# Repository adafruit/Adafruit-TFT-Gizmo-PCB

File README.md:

## Adafruit Circuit Playground TFT Gizmo - Bolt-on Display + Audio Amplifier PCB

<a href="http://www.adafruit.com/products/4367"><br/>
Click here to purchase one from the Adafruit shop</a>

PCB files for the Adafruit Circuit Playground TFT Gizmo - Bolt-on Display + Audio Amplifier. 

Format is EagleCAD schematic and board layout
* https://www.adafruit.com/product/4367

### Description

Extend and expand your Circuit Playground projects with a bolt on TFT Gizmo that lets you add a lovely color display in a sturdy and reliable fashion. This PCB looks just like a round TFT breakout but has permanently affixed M3 standoffs that act as mechanical and electrical connections.

Once attached you'll get a 1.54" 240x240 IPS display with backlight control, two 3-pin STEMMA connectors for attaching NeoPixel strips or servos, and a Class D audio amplifier with a Molex PicoBlade connector that can plug one of our lil speakers.

This is a great companion for our Circuit Playground Express or Bluefruit boards thanks to their fast SPI hardware speeds, and works in Arduino and CircuitPython. You can use it with the Circuit Playground Classic but it won't be very fast, as you have to bitbang the SPI - and the display has a lot of pixels - so it's not recommended.

Comes with a PCB that has pre-soldered standoffs attached, and 12x M3 screws for attachment. Fits all Circuit Playgrounds but like we mentioned earlier, the Express and Bluefruit are recommended.

### License

Adafruit invests time and resources providing this open source design, please support Adafruit and open-source hardware by purchasing products from [Adafruit](https://www.adafruit.com)!

Designed by Limor Fried/Ladyada for Adafruit Industries.

Creative Commons Attribution/Share-Alike, all text above must be included in any redistribution. 
See license.txt for additional details.

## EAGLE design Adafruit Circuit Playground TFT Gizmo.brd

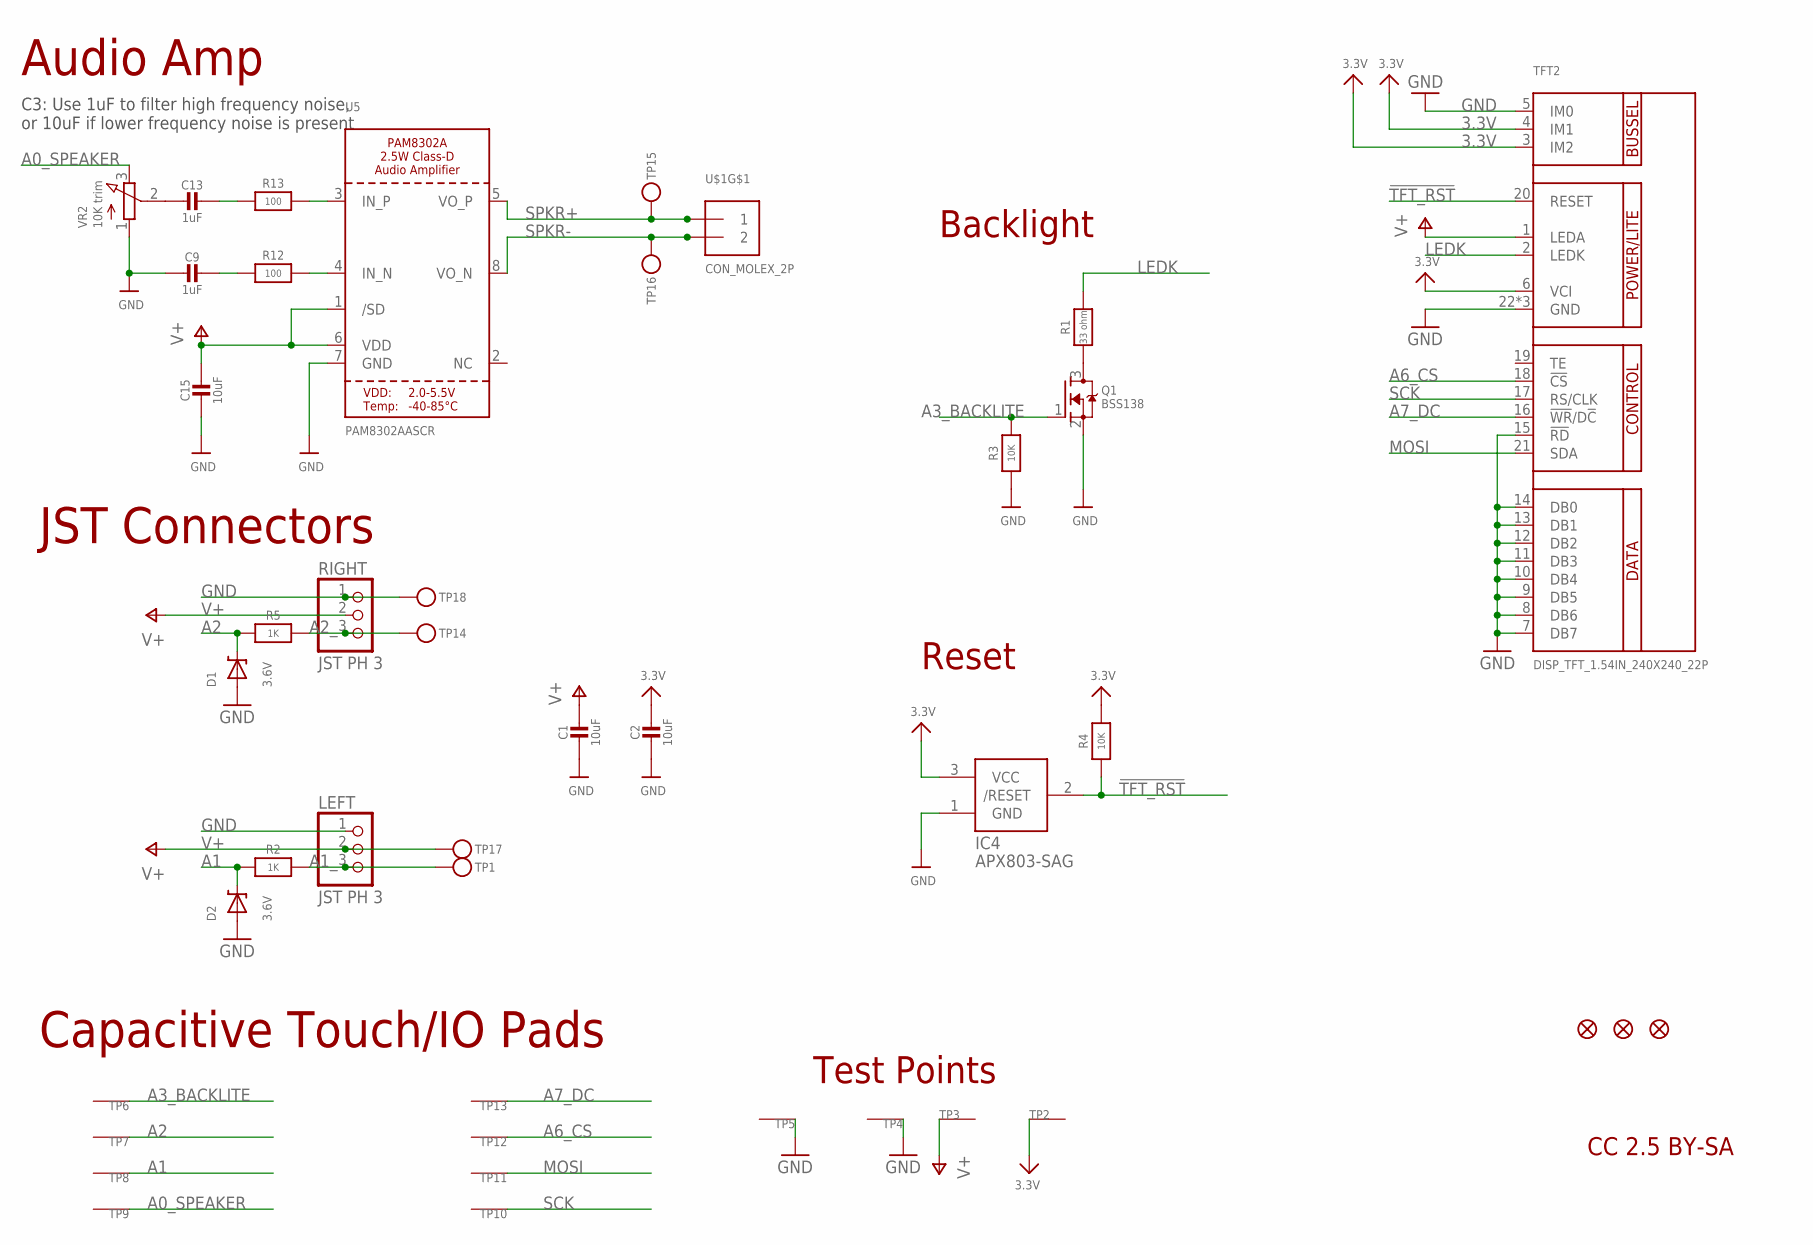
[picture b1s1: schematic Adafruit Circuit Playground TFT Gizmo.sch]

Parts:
C1, C2, C15: 10uF; 0805-NO
C9, C13: 1uF; 0603-NO
D1, D2: 3.6V; SOD-323
IC4: APX803-SAG; SOT23
LEFT: JST PH 3; JSTPH3
Q1: BSS138; SOT23-WIDE
R1: 33 ohm; 0603-NO
R2, R5: 1K; 0603-NO
R3, R4: 10K; 0603-NO
R12, R13: 100; 0603-NO
RIGHT: JST PH 3; JSTPH3
TFT2: DISP_TFT_1.54IN_240X240_22P; TFT_1.54IN_240X240_22PIN
TP1, TP14, TP15, TP16, TP17, TP18: TESTPOINTROUND1.5MMNO; TESTPOINT_ROUND_1.5MM_NO
TP2, TP3, TP4, TP5, TP6, TP7, TP8, TP9, TP10, TP11, TP12, TP13: SEWTAP_SMTNUTM3; SMT_NUT_3MM
U5: PAM8302AASCR; MSOP8_0.65MM
U$1: CON_MOLEX_2P; 53398-0271
U$2, U$3, U$6: FIDUCIAL_1MM
VR2: 10K trim; TRIMPOT_BOURNS_3303W

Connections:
3.3V: C2.1, IC4.3 (VCC), R4.2, TFT2.3 (IM2), TFT2.4 (IM1), TFT2.6 (VCI), TP2.P$1
!TFT_RST: IC4.2 (/RESET), R4.1, TFT2.20 (RESET)
A0_SPEAKER: TP9.P$1, VR2.3 (E)
A1: D2.C, R2.2, TP8.P$1
A1_: LEFT.3, R2.1, TP1.P$1
A2: D1.C, R5.2, TP7.P$1
A2_: R5.1, RIGHT.3, TP14.P$1
A3_BACKLITE: Q1.1 (G), R3.2, TP6.P$1
A6_CS: TFT2.18 (!CS), TP12.P$1
A7_DC: TFT2.16 (!WR!/D!C), TP13.P$1
GND: C1.2, C2.2, C9.2, C15.2, D1.A, D2.A, IC4.1 (GND), LEFT.1, Q1.2 (S), R3.1, RIGHT.1, TFT2.5 (IM0), TFT2.7 (DB7), TFT2.8 (DB6), TFT2.9 (DB5), TFT2.10 (DB4), TFT2.11 (DB3), TFT2.12 (DB2), TFT2.13 (DB1), TFT2.14 (DB0), TFT2.15 (!RD), TFT2.22 (GND), TFT2.SUPPORT1 (GND), TFT2.SUPPORT2 (GND), TP4.P$1, TP5.P$1, TP18.P$1, U5.7 (GND), VR2.1 (A)
LEDK: R1.2, TFT2.2 (LEDK)
MOSI: TFT2.21 (SDA), TP11.P$1
unnamed: Q1.3 (D), R1.1
unnamed: R12.2, U5.4 (IN_N)
unnamed: R13.2, U5.3 (IN_P)
unnamed: C9.1, R12.1
unnamed: C13.1, R13.1
unnamed: C13.2, VR2.2 (S)
SCK: TFT2.17 (RS/CLK), TP10.P$1
SPKR+: TP15.P$1, U5.5 (VO_P), U$1.1
SPKR-: TP16.P$1, U5.8 (VO_N), U$1.2
V+: C1.1, C15.1, LEFT.2, RIGHT.2, TFT2.1 (LEDA), TP3.P$1, TP17.P$1, U5.1 (/SD), U5.6 (VDD)

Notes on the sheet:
CC 2.5 BY-SA
Capacitive Touch/IO Pads
C3: Use 1uF to filter high frequency noise, or 10uF if lower frequency noise is present
Audio Amp
JST Connectors
Test Points
Reset
Backlight

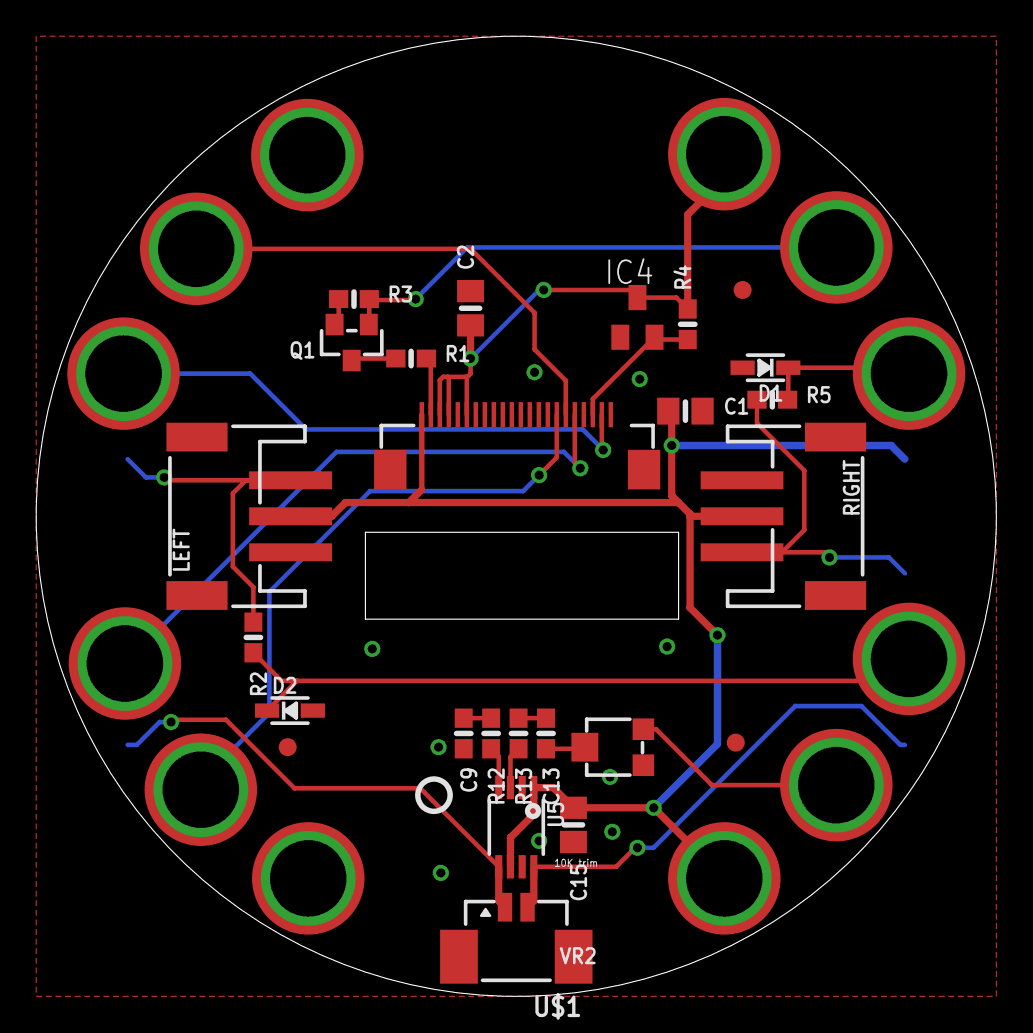
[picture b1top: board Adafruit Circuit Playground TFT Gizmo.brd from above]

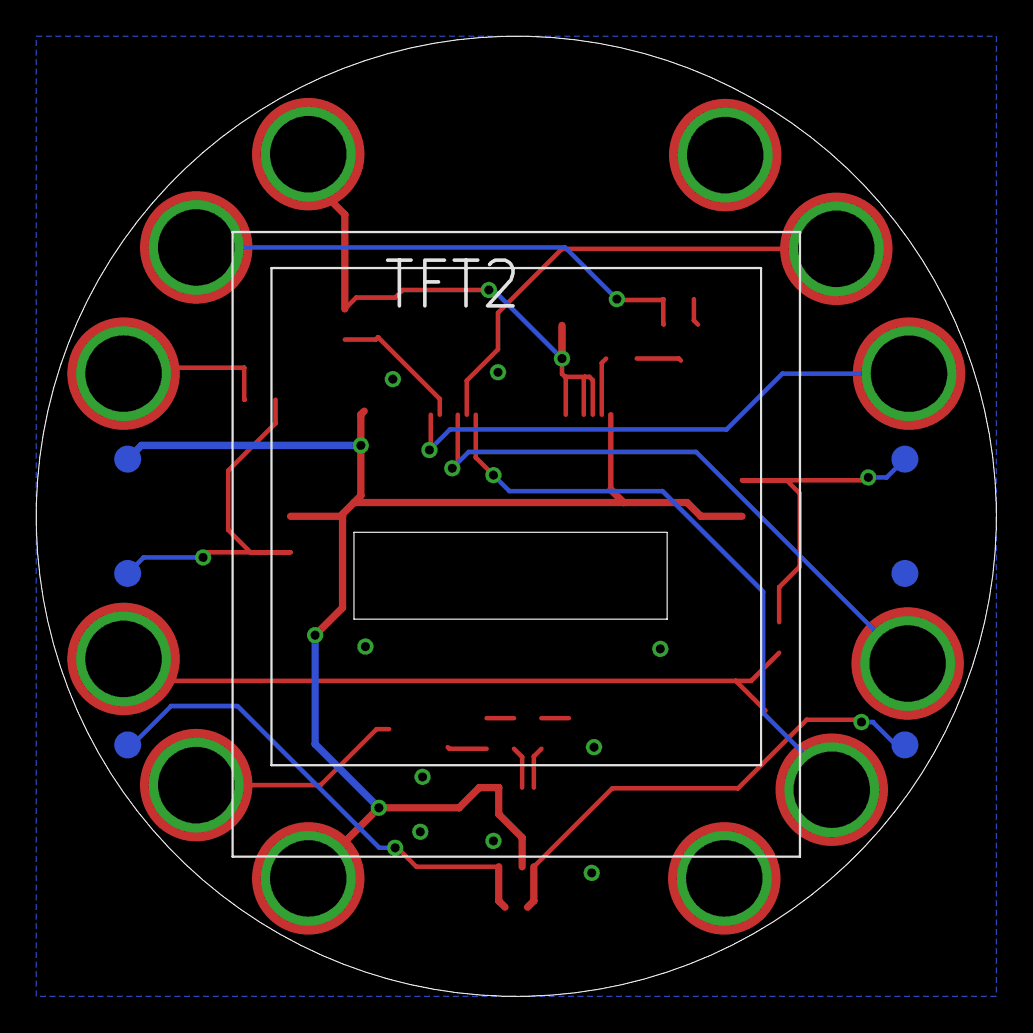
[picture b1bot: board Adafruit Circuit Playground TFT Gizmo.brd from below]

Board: 2 copper layers, 53.3 x 53.3 mm, 46 parts (8 on the bottom side), 23 nets.

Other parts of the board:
U$7: PCBFEAT-REV-040
U$17: TFTGIZMO_FRONT
U$18: TFTGIZMO_BACK

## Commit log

2019-10-03 Adding board files
2019-10-03 Updated to D1 Revision

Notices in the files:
parts and their libraries:
microbuilder: This work is placed in the public domain, and may be freely used for commercial and non-commercial work with the following conditions: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
